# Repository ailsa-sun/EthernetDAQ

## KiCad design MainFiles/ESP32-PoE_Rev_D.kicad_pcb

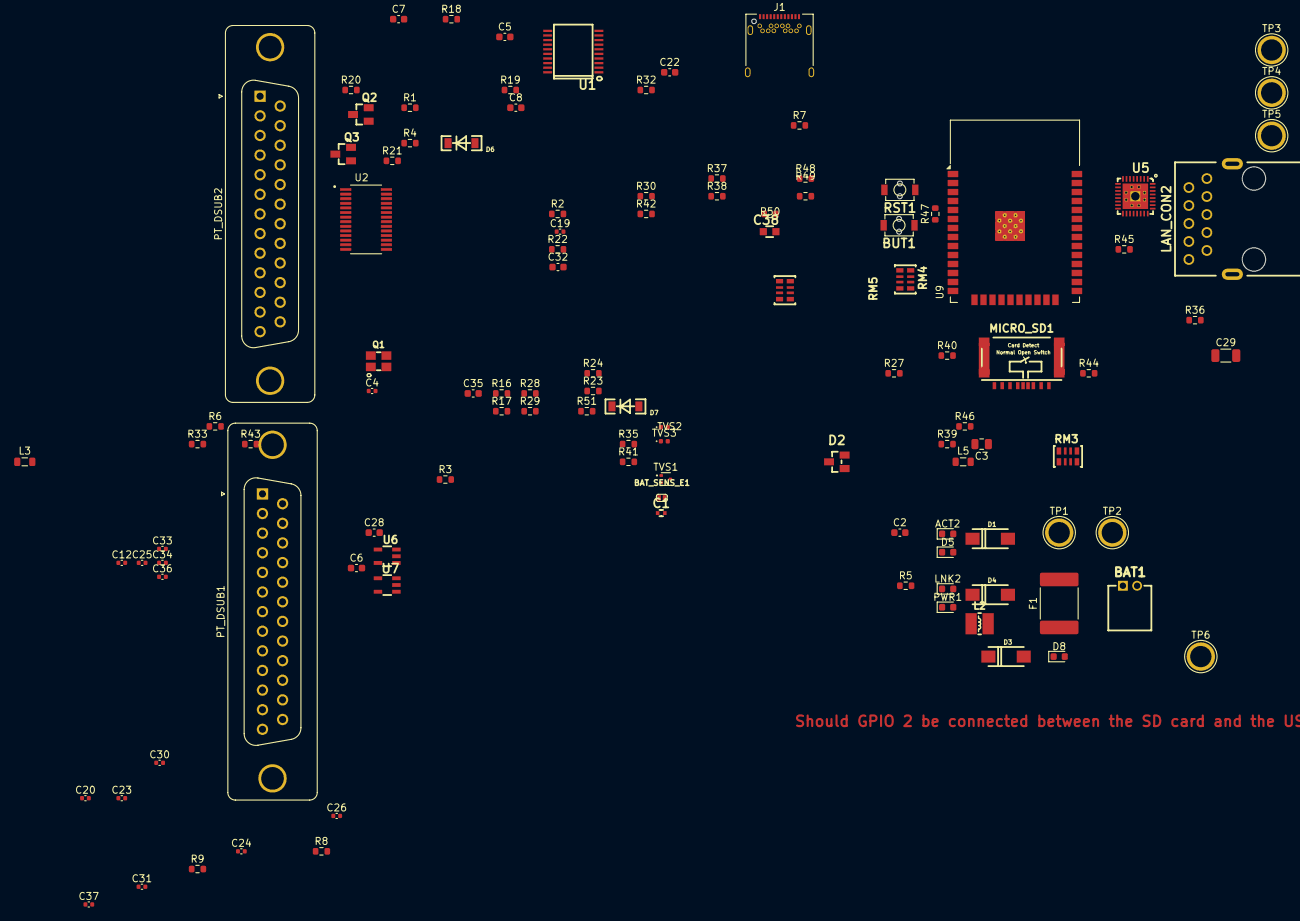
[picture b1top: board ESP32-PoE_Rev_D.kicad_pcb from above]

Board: 2 copper layers, 114 parts (1 on the bottom side), 99 nets, no tracks yet.

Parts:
ACT2: LED/YELLOW/0603; D_0603_1608Metric
BAT1: DW02R; LIPO_BAT-CON2DW02R
BAT_SENS_E1: Opened; SJ_1_SMALLER
BUT1: IT1185AU2; IT1185AU2_V2
C1: 4.7 pf; C_0402_5MIL_DWS
C2: 22uF; C_0603_1608Metric
C3: 47uF/6.3V/20%/X5R/C0805; C_0805_2012Metric
C4: 27pF/50V/5%/C0G/C0402; C_0402_1005Metric
C5: 27pF/50V/5%/C0G/C0402; C_0603_1608Metric
C6, C7, C22, C28, C32: 22uF/6.3V/20%/X5R/C0603; C_0603_1608Metric
C8: 100nF/16V/10%/X7R/C0402; C_0603_1608Metric
C12, C23, C24, C26: 1 uF; C_0402_1005Metric
C19: 1nF/50V/10%/X7R/C0402; C_0402_1005Metric
C20, C25: 0.1 uF; C_0402_1005Metric
C29: 1nF/2000V/10%/X7R/C1206; C_1206_3216Metric
C30, C31, C33, C34, C36, C37: 100nF/16V/10%/X7R/C0402; C_0402_1005Metric
C35: 2.2uF/6.3V/10%/X5R/C0603; C_0603_1608Metric
C38: NA(10uF/6.3V/20%/X5R/C0603); C_0603_5MIL_DWS
D1, D3, D4: 1N5822/SS34/SMA; SMA-KA
D2: BAT54C(SOT23-3); SOT23-3
D5, D8: D_Small; D_0603_1608Metric
D6, D7: 1N5819S4(SOD-123); SOD-123_1C-2A_KA
F1: 6A Fuse; Fuse_2920_7451Metric
J1: USB_C_Receptacle_USB2.0; USB_C_Receptacle_Amphenol_12401548E4-2A
L2: 2.2uH/1.5A/DCR=72mR/20%/3.00x3.00x1.50mm/CD32(NR3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; CD32
L3, L5: FB0805/600R/2A; L_0805_2012Metric
LAN_CON2: RJP-003TC1(LPJ4112CNL)
LNK2: LED/GREEN/0603; D_0603_1608Metric
MICRO_SD1: TFC-9P-1.7H(ATFFS150A01BR016); uSD(TFC-9P-1.xH(ATFFS150A01BR016))
PT_DSUB1, PT_DSUB2: DB25_Receptacle; DSUB-25_Female_Vertical_P2.77x2.84mm_MountingHoles
PWR1: LED/RED/0603; D_0603_1608Metric
Q1: Q12MHz/20pF/10ppm/4P/3.2x2.5mm; TSX-3.2x2.5mm_GND(3)
Q2, Q3: BC817-40(SOT23); SOT23
R1, R18, R19, R39, R48, R50: 10k/R0402; R_0603_1608Metric
R2: 10k; R_0603_1608Metric
R3, R6, R8, R27, R28, R33: 47; R_0603_1608Metric
R4: 47k/R0402; R_0603_1608Metric
R5, R41, R42, R45: 2.2k/R0402; R_0603_1608Metric
R7, R23: R_Small; R_0603_1608Metric
R9: 100k/R0402; R_0603_1608Metric
R16: NA(10k/R0402); R_0603_1608Metric
R17, R22, R32: 470k/R0402; R_0603_1608Metric
R20, R21: 1k/R0402; R_0603_1608Metric
R24, R46, R47: 220R/R0402; R_0603_1608Metric
R29: 220k/R0402; R_0603_1608Metric
R30: 49.9k/1%/R0402; R_0603_1608Metric
R35, R36, R37, R38: 49.9R/1%/R0402; R_0603_1608Metric
R40, R43: 10R/R0402; R_0603_1608Metric
R44, R49: NA/R0402; R_0603_1608Metric
R51: 12.1k/1%/R0402; R_0603_1608Metric
RM3, RM4, RM5: RA1206_(4X0603)_4B8_2.2k; R_MATRIX_4
RST1: IT1185AU2; IT1185AU2_V2
Sign_Antistatic: Val**; LOGO_ANTISTATIC_1
TP1, TP2: TestPoint_Small; TestPoint_Plated_Hole_D3.0mm
TP3, TP4, TP5, TP6: Mounting Hole; TestPoint_Plated_Hole_D3.0mm
TVS1: ESDS314DBVR(SOT-23-5); SOT-523
TVS2, TVS3: NA(GG0402052R542P); D_0402_1005Metric
U1: CH340T(SSOP20W); SSOP-20W
U2: ADS1263IPWR; SOP65P640X120-28N
U5: LAN8710A-EZC(QFN32); QFN32_EP(33)_5.00x5.00x0.90mm_Pitch_0.50mm
U6: SN74LVC1G04DBVR(SOT23-5); SOT-23-5
U7: SY8089AAAC(SOT23-5); SOT-23-5
U9: ESP-WROOM-32; ESP32-WROOM-32

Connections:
+3.3VLAN: C28.1, C31.1, C37.2, L3.1, R50.2, RM4.1.1, RM4.2.1, RM4.3.1, RM4.4.1, RM5.3.1, U5.12 (VDDIO), U6.5 (VCC)
+3V3: C22.1, C25.1, C26.1, L2.2, L5.1, R16.2, R29.2, R32.1, R39.1, R44.2, R48.1, RM3.1.2, RM3.2.2, RM3.3.2, RM3.4.2, U2.19 (DVDD), U9.2 (3V3)
/+5V_USB: C7.1, D1.2 (A), J1.A4 (VBUS), J1.A9 (VBUS), J1.B4 (VBUS), J1.B9 (VBUS), R18.1, U1.19 (VCC)
/D_Com: D2.3 (CC), R24.2, R49.2
/ESP_EN: Q2.3 (C), R32.2, RST1.1, U9.3 (EN)
/GPI34\BUT1: BUT1.1, R48.2, R49.1, U9.6 (GPI34/ADC1_CH6/RTC_GPIO4)
/GPI35: BAT_SENS_E1.1, U9.7 (GPI35/ADC1_CH7/RTC_GPIO5)
/GPI39: R4.2, R9.1, U9.5 (GPI39/SENSOR_VN/ADC1_CH3/ADC_H/RTC_GPIO3)
/GPIO0: D2.2 (A2), R44.1, U6.2 (A), U9.25 (GPIO0/ADC2_CH1/TOUCH1/RTC_GPIO11/CLK_OU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)
/GPIO1\U0TXD: D7.1 (K), U9.35 (GPIO1/U0TXD/CLK_OUT3/EMAC_RXD2)
/GPIO2\HS2_DATA0: D2.1 (A1), R46.1, RM3.4.1, U9.24 (GPIO2/ADC2_CH2/TOUCH2/RTC_GPIO12/HSPIWP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)
/GPIO3\U0RXD: D6.2 (A), R16.1, R19.2, U9.34 (GPIO3/U0RXD/CLK_OUT2)
/GPIO4\U1TXD: R28.1, U9.26 (GPIO4/ADC2_CH0/TOUCH0/RTC_GPIO10/HSPIHD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)
/GPIO5\SPI_CS: R8.1, U9.29 (GPIO5/VSPICS0/HS1_DATA6/EMAC_RX_CLK)
/GPIO10: R3.1, U9.18 (GPIO10/SD_DATA3/SPIWP/HS1_DATA3/U1TXD)
/GPIO14\HS2_CLK: R40.1, U9.13 (GPIO14/ADC2_CH6/TOUCH6/RTC_GPIO16/MTMS/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)
/GPIO15\HS2_CMD: MICRO_SD1.3 (CMD/DI), R39.2, U9.23 (GPIO15/ADC2_CH3/TOUCH3/MTDO/HSPICS0/RTC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)
/GPIO16\I2C-SCL: R6.1, R43.2, U9.27 (GPIO16/HS1_DATA4/U2RXD/EMAC_CLK_OUT)
/GPIO17\EMAC_CLK_OUT_180: U5.5 (XTAL1/CLKIN), U6.4 (Y), U9.28 (GPIO17/HS1_DATA5/U2TXD/EMAC_CLK_OUT_180)
/GPIO18\MDIO(RMII): RM4.4.2, U5.16 (MDIO), U9.30 (GPIO18/VSPICLK/HS1_DATA7)
/GPIO19\EMAC_TXD0(RMII): U5.22 (TXD0), U9.31 (GPIO19/VSPIQ/U0CTS/EMAC_TXD0)
/GPIO21\EMAC_TX_EN(RMII): U5.21 (TXEN), U9.33 (GPIO21/VSPIHD/EMAC_TX_EN)
/GPIO22\EMAC_TXD1(RMII): U5.23 (TXD1), U9.36 (GPIO22/VSPIWP/U0RTS/EMAC_TXD1)
/GPIO23\MDC(RMII): U5.17 (MDC), U9.37 (GPIO23/VSPID/HS1_STROBE)
/GPIO25\EMAC_RXD0(RMII): RM4.2.2, U5.11 (RXD0/MODE0), U9.10 (GPIO25/DAC_1/ADC2_CH8/RTC_GPIO6/EMAC_RX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)
/GPIO26\EMAC_RXD1(RMII): RM4.1.2, U5.10 (RXD1/MODE1), U9.11 (GPIO26/DAC_2/ADC2_CH9/RTC_GPIO7/EMAC_RX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)
/GPIO27\EMAC_RX_CRS_DV: RM4.3.2, U5.15 (COL/CRS_DV/MODE2), U9.12 (GPIO27/ADC2_CH7/TOUCH7/RTC_GPIO17/EMAC_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)
/GPIO32: R27.1, U9.8 (GPIO32/XTAL_32K_P/ADC1_CH4/TOUCH9/RTC_G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)
/GPIO33: R33.2, R43.1, U9.9 (GPIO33/XTAL_32K_N/ADC1_CH5/TOUCH8/RTC_G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)
/RD+: LAN_CON2.3 (RD+), R36.2, TVS1.1 (I/O1), TVS3.1 (IO1), U5.31 (RXP)
/RD-: LAN_CON2.6 (RD-), R35.2, TVS3.2 (IO2), U5.30 (RXN)
/TD+: LAN_CON2.1 (TD+), R38.2, TVS1.3 (I/O2), TVS2.2 (IO2), U5.29 (TXP)
/TD-: LAN_CON2.2 (TD-), R37.2, TVS2.1 (IO1), U5.28 (TXN)
unnamed: ACT2.2 (A), U5.3 (LED1/REGOFF)
unnamed: ACT2.1 (K), R42.1
unnamed: BAT_SENS_E1.2, C19.1, R17.2, R22.1
unnamed: BUT1.2, R47.1
unnamed: C6.1, D3.1 (K), U7.1 (EN), U7.4 (IN)
unnamed: BAT1.1, D4.2 (A)
unnamed: D4.1 (K), R17.1
unnamed: D5.2 (A), R2.1
unnamed: C2.2, D5.1 (K), D8.2 (A), F1.1
unnamed: D6.1 (K), U1.3 (TXD)
unnamed: D7.2 (A), R18.2, U1.4 (RXD)
unnamed: F1.2, TP1.1
unnamed: J1.A5 (CC1), R7.1
unnamed: J1.B5 (CC2), R23.1
unnamed: C30.1, C32.1, C33.1, C34.1, L3.2, LAN_CON2.4 (TCT), LAN_CON2.5 (RCT), R35.1, R36.1, R37.1, R38.1, R41.1, U5.1 (VDD2A), U5.27 (VDD1A)
unnamed: C29.2, LAN_CON2.0 (Shield)
unnamed: LNK2.2 (A), R41.2
unnamed: LNK2.1 (K), U5.2 (LED2/NINTSEL)
unnamed: MICRO_SD1.2 (CD/DAT3/CS), RM3.2.1
unnamed: MICRO_SD1.5 (CLK/SCLK), R40.2
unnamed: MICRO_SD1.7 (DAT0/DO), R46.2
unnamed: MICRO_SD1.8 (DAT1/RES), RM3.1.1
unnamed: MICRO_SD1.1 (DAT2/RES), RM3.3.1
unnamed: C3.1, L5.2, MICRO_SD1.4 (VDD)
unnamed: PWR1.1 (K), R5.1
unnamed: Q2.1 (B), R20.2
unnamed: Q2.2 (E), R21.1, U1.16 (RTS#)
unnamed: Q3.1 (B), R21.2
unnamed: Q3.3 (C), R24.1
unnamed: Q3.2 (E), R20.1, U1.15 (DTR#)
unnamed: J1.A6 (D+), J1.B6 (D+), U1.6 (UD+)
unnamed: J1.A7 (D-), J1.B7 (D-), U1.7 (UD-)
unnamed: C8.1, R19.1, U1.5 (V3)
unnamed: C4.1, Q1.1, U1.9 (XI)
unnamed: C5.1, Q1.2, U1.10 (XO)
unnamed: C12.1, U2.17 (BYPASS)
unnamed: C1.1, U2.5 (CAPN)
unnamed: C1.2, U2.4 (CAPP)
unnamed: R6.2, U2.10 (CS)
unnamed: R27.2, U2.12 (DIN)
unnamed: R33.1, U2.13 (DOUT/DRDY)
unnamed: R8.2, U2.14 (DRDY)
unnamed: C24.2, U2.8 (REFOUT)
unnamed: R3.2, U2.20 (RESET/PWDN)
unnamed: R28.2, U2.11 (SCLK)
unnamed: C38.2, R50.1, U5.19 (NRST)
unnamed: R51.1, U5.32 (RBIAS)
unnamed: RM5.1.2, U5.7 (RXCLK/PHYAD1)
unnamed: RM5.3.2, U5.9 (RXD2/RMIISEL)
unnamed: RM5.2.2, U5.8 (RXD3/PHYAD2)
unnamed: R45.2, U5.13 (RXER/RXD4/PHYAD0)
unnamed: C35.1, C36.1, U5.6 (VDDCR)
unnamed: R29.1, R30.1, U7.5 (FB)
unnamed: L2.1, U7.3 (LX)
PT1_A+: PT_DSUB1.14, U2.22 (AIN1)
PT1_E+: C20.1, C23.1, D1.1 (K), D3.2 (A), D8.1 (K), PT_DSUB1.1, PT_DSUB1.3, PT_DSUB1.5, PT_DSUB1.7, PT_DSUB1.9, PT_DSUB1.11, PWR1.2 (A), R1.1, R4.1, U2.6 (AVDD)
PT1_E-: BAT1.2, C2.1, C3.2, C4.2, C5.2, C6.2, C7.2, C8.2, C12.2, C19.2, C20.2, C22.2, C23.2, C24.1, C25.2, C26.2, C28.2, C29.1, C30.2, C31.2, C32.2, C33.2, C34.2, C35.2, C36.2, C37.1, C38.1, J1.A1 (GND), J1.A12 (GND), J1.B1 (GND), J1.B12 (GND), J1.S1 (SHIELD), LAN_CON2.7 (GND/NC), LAN_CON2.8 (NC/GND), MICRO_SD1.6 (GND), MICRO_SD1.CH1 (Card_Housing), PT_DSUB1.2, PT_DSUB1.4, PT_DSUB1.6, PT_DSUB1.8, PT_DSUB1.10, PT_DSUB1.12, Q1.3 (case), R1.2, R2.2, R5.2, R7.2, R9.2, R22.2, R23.2, R30.2, R42.2, R45.1, R47.2, R51.2, RM5.1.1, RM5.2.1, RST1.2, TP2.1, TVS1.2 (GND), U1.8 (GND), U2.7 (AVSS), U2.16 (XTAL2), U2.18 (DGND), U5.24 (TXD2), U5.25 (TXD3), U5.33 (GND), U6.3 (GND), U7.2 (GND), U9.1 (GND), U9.15 (GND), U9.38 (GND), U9.39 (THERMAL_PAD)
PT2_A+: PT_DSUB1.16, U2.23 (AIN2)
PT3_A+: PT_DSUB1.18, U2.24 (AIN3)
PT4_A+: PT_DSUB1.20, U2.25 (AIN4)
PT5_A+: PT_DSUB1.22, U2.26 (AIN5)
PT6_A+: PT_DSUB1.24, U2.27 (AIN6)
PT7_A+: PT_DSUB2.14, U2.28 (AIN7)
PT8_A+: PT_DSUB2.16, U2.1 (AIN8)
PT9_A+: PT_DSUB2.18, U2.2 (AIN9)
PT10_A+: PT_DSUB2.20, U2.21 (AINO)

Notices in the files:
MainFiles/ESP32-PoE_Rev_D.kicad_pcb:
(C) 2019
